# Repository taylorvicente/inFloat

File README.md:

# inFloat

Full hardware and firmware suite for the inFloat electronics package (Purdue ME 463).

When the float deploys, the electronics detect it with a Hall-effect switch, power up a 5 V boost rail, flash the survivor lights and send an alert with location data over LTE-M.

## Hardware

| Component | Purpose |
| --- | --- |
| Seeed XIAO ESP32S3 | Main MCU, running MicroPython |
| M5Stack CatM + American LTE-M microSIM | Cellular alert link |
| Survivor Light board | LED beacon, driven with PWM |
| 5 V MiniBoost | Powers the CatM and survivor lights after deployment |
| 400 mAh 3.7 V LiPo | Battery |
| Hall sensor switch | Detects deployment when the magnet moves away |

### Pin map (XIAO ESP32S3)

| GPIO | Signal | Direction |
| --- | --- | --- |
| 1 | Battery voltage (ADC, through a 1:2 divider) | In |
| 2 | Hall sensor | In |
| 3 | Communication / 5 V boost enable | Out |
| 4 | Survivor light PWM | Out |
| D6 / D7 | UART0 TX / RX to the CatM | UART |

## Repository layout

```
Electronics.kicad_*        Top-level system schematic (KiCad 10)
SurvivorLight/             Survivor Light LED board (schematic + PCB)
libraries/
  inFloat_Custom.pretty/   Custom footprints used by the boards
Code/
  esp32.py                 Main MicroPython firmware (work in progress)
  firmware/                MicroPython image for the ESP32-S3 (v1.29.0, octal SPIRAM)
```

## Hardware design files

The schematics and PCBs are KiCad 10 projects. Before opening them, add the footprint library:

1. In KiCad, open **Preferences → Manage Footprint Libraries**.
2. Add `libraries/inFloat_Custom.pretty` with the nickname `inFloat_Custom`.

The XIAO ESP32S3 symbol (`Seeed_Studio_XIAO_Series`) comes from the [OPL KiCad Library](https://github.com/Seeed-Studio/OPL_Kicad_Library), so install that as well.

## Firmware: getting started

1. Install the tools: `pip install esptool mpremote`
2. Flash MicroPython (replace the port with yours):
   ```sh
   esptool.py --chip esp32s3 --port /dev/cu.usbmodem* erase_flash
   esptool.py --chip esp32s3 --port /dev/cu.usbmodem* write_flash -z 0 \
     Code/firmware/ESP32_GENERIC_S3-SPIRAM_OCT-20260824-v1.29.0.bin
   ```
3. Upload and run the firmware:
   ```sh
   mpremote cp Code/esp32.py :main.py
   mpremote reset
   ```

## Firmware status

- [ ] Battery state of charge
- [ ] Deployment detection (poll the Hall sensor at 5 Hz)
- [ ] 5 V boost / CatM enable on deployment
- [ ] Survivor light flashing at 20% duty cycle
- [ ] LTE-M alert (JSON with location), retried until delivery is confirmed
- [ ] Main loop

## Author

Taylor Vicente

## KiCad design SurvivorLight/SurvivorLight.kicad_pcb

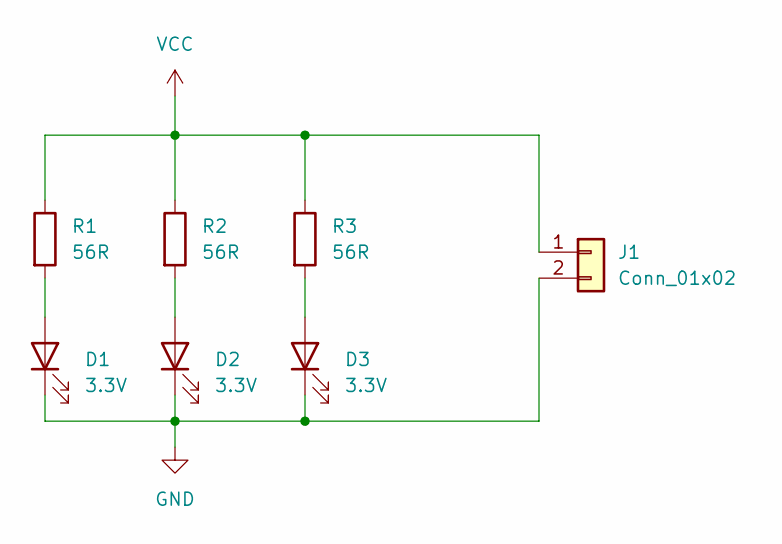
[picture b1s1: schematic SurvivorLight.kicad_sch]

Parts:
D1, D2, D3: 3.3V; LW_G6SP_HandSolder
J1: Conn_01x02; PinHeader_1x02_P2.54mm_Vertical
R1, R2, R3: 56R; R_01005_0402Metric_Pad0.57x0.30mm_HandSolder

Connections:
GND: D1.1 (K), D2.1 (K), D3.1 (K), J1.2
unnamed: D1.2 (A), R1.2
unnamed: D2.2 (A), R2.2
unnamed: D3.2 (A), R3.2
VCC: J1.1, R1.1, R2.1, R3.1

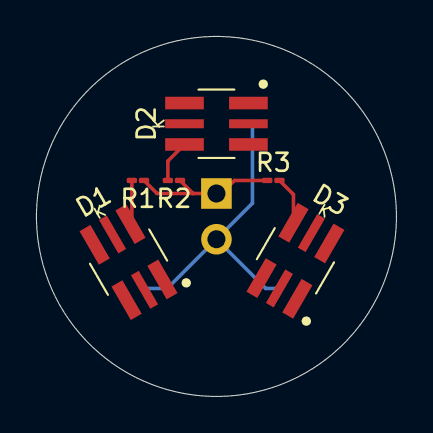
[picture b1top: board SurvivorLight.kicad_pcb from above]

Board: 2 copper layers, 20.0 x 20.0 mm, 7 parts (1 on the bottom side), 5 nets.
